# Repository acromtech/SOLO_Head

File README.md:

# SOLO_Head

## Assembly

<br>*Note : Equations can be used to re-size head diameter*

## Design Parts
| CAO | Print | Printing time | Name | Filament | Comment |
|:---:|:---:|---|---|---|---|
|  |  | 9h | 1x Head_Top | ABS | 45° touching buildplate supports required (use soluble supports is better) |
|  | | 1min | 1x Head_Joint | Neoprene | made with laser cutter machine |
|  || 33min | 2x Microphone_Joint | TPU | 45° touching buildplate supports required (use soluble supports is better) |
|  || 20min | 4x Camera_Spacer<br>4x CM4_Spacer<br>8x uDriver_Spacer | ABS | No support required |
|  |  | 1h | 1x Board_Mount | ABS | No support required |
|  |  | 5min | 1x End_Stop | ABS | No support required |
|  | | 1h30 | 1x Encoder_Mount | ABS | No support required |
|  |  | 20min | 1x Encoder_Adaptator | ABS | No support required |
|  |  | 12h | 1x Head_Bottom | ABS | 45° touching buildplate supports required (use soluble supports is better) |
|  || 4h | 1x Head_Stand | ABS | No support required but print with soluble support is better |

## Generic Parts
| Screen | Reference | Link | Comment |
|:---:|---|---|---|
||1x 6700-2RS ball bearing<br>Ø10xØ15x4mm|[123Roulement](https://www.123roulement.com/roulements-6700-2RS)|To link "Encoder_Mount" and "Encoder_Adaptator" design parts|
||8x TCHC M3x8 Screw|[Fixnvis](https://www.visseriefixations.fr/vis-a-six-pans-creux/tete-fraisee-hexagonale-creuse/inox-a4/tfhc-m3x8-inox-a4-ef-din-7991.html)|To link "Encoder_Mount" design part and the motor<br>To link "Encoder_Mount" and "Head_Bottom" design parts|
||4x TCHC M2.5x20 Screw|[Fixnvis](https://www.visseriefixations.fr/vis-a-six-pans-creux/tete-fraisee-hexagonale-creuse/inox-a4/tfhc-m2-5x20-inox-a4-din-7991.html)|To link "Board_Mount" with spacers and "Head_Bottom" design parts|
||1x AEDB-9140-A13 Broadcom Encoder|[RS](https://fr.rs-online.com/web/p/codeurs/7967806?cm_mmc=FR-PLA-DS3A-_-google-_-CSS_FR_FR_Automatisme_et_Controle_de_process_Whoop-_-(FR:Whoop!)+Codeurs-_-7967806&matchtype=&pla-371581285844&gclid=Cj0KCQjw4uaUBhC8ARIsANUuDjVO7Ht5YMR8SH6bczQU4esH6yAVaWhDGcGdfncjnVxadasoeFgfhUsaAsJuEALw_wcB&gclsrc=aw.ds)|/|
||1x GB4106 Tmotor motor|[Hexadrone](https://hexadrone.fr/gamme-gimbal-nacelle/509-moteur-brushless-nacelle-gb4106-tmotor-6971360351184.html)|/|
||1x Arducam 2MP Global Shutter OG02B10 Pivariety camera module |[Robotshop](https://www.robotshop.com/be/fr/module-camera-couleur-arducam-2mp-global-shutter-og02b10-pivariety.html)|/|
||1x ArduCam M12 camera lens (6pcs)|[Robotshop](https://www.robotshop.com/be/fr/kit-objectif-arducam-m12-pour-camera-hq-20-180deg-6pcs.html)|/|
||1x CM4 Raspberry Pi|[Kubii](https://www.kubii.fr/cartes-raspberry-pi/3086-raspberry-pi-compute-module-4-3272496302952.html)|/|
||2x Microphone module|/|Electronic CAD are in the repository "hardware"|
||2x uDriver board||[ODRI repository](https://github.com/open-dynamic-robot-initiative/open_robot_actuator_hardware/blob/master/electronics/micro_driver_electronics/README.md#micro-driver-electronics)|
||2x DF13-5S-1.25C Hirose connector|[RS components](https://fr.rs-online.com/web/p/boitiers-de-connecteurs-pour-circuits-imprimes/1113616)|To link uDriver and communication cables<br>To link CM4 Raspberry Pi and communication cables|
||1x DF13-5P-1.25DS Hirose connector|[RS components](https://fr.rs-online.com/web/p/embases-circuits-imprimes/7793529)|To change encoder connector|
||1x DF13-5P-1.25DSA Hirose connector|[RS components](https://fr.rs-online.com/web/p/embases-circuits-imprimes/5037912)|To link head CM4 Raspberry Pi shield communication cables to body Raspberry Pi communication cables|
||1x RE-6619107 XT30U 2 mm Reely Male  connector|[Conrad](https://www.conrad.fr/p/reely-re-6619107-fiche-male-pour-batterie-xt30u-2-mm-femelle-doree-a-souder-1-pcs-2206369)|To link power cables to uDriver board|
||1x RE-6619104 XT30U 2 mm Reely Female connector|[Conrad](https://www.conrad.fr/p/reely-re-6619107-fiche-male-pour-batterie-xt30u-2-mm-femelle-doree-a-souder-1-pcs-2206369)|To link power cables to power board (on SOLO body)|
||1x Kabeltronik 160110009-1 1mm² Black Power Wire|[Conrad](https://www.conrad.com/p/kabeltronik-160110009-1-strand-lify-1-x-1-mm-black-sold-per-metre-323735)|To power uDriver board|
||1x Kabeltronik 160110008 1mm² Red Power Wire|[Conrad](https://www.conrad.fr/p/fil-de-cablage-lify-kabeltronik-160110008-1-1-x-1-mm-rouge-marchandise-vendue-au-metre-323734)|To power uDriver board|
||1x 10 way 3M 3302-10 100FT communication cables |[RS components](https://fr.rs-online.com/web/p/cables-en-nappe/1055281)|To link encoder and uDriver (5 way)<br>To link CM4 Raspberry Pi and uDriver (5 way)|
||1x DF13-2630SCF 0.12mm² Hirose DF13 Crimp Terminals|[RS components](https://fr.rs-online.com/web/p/cables-en-nappe/1055281)|To link communication cables with DF13-5S-1.25C Hirose connector|
||1x DF13-TB2630HC Hirose Crimping Tool for DF13 Crimp Terminals |[RS components](https://fr.rs-online.com/web/p/cables-en-nappe/1055281)|To link communication cables with DF13-5S-1.25C Hirose connector|

## Next Version (V7)
To reduce mass, clean print, and keep design apparence. I realize some modifications on the V6 design :
* Delete "Head_Joint" neoprene gasket and chamfer "Head_Bottom" and "Head_Top" parts to simplify the model and clean model surface.
* Design a new "Head_Stand" to link the SOLO's head to SOLO's body.
* Delete "Microphone_Joint" and integrate a screwing system on "Head_Bottom" to simplify the model. To limit microphone noise, generic O-rings are positioned on the screw.
* Upgrade clips shape to limit printing supports.

## License
BSD 3-Clause License

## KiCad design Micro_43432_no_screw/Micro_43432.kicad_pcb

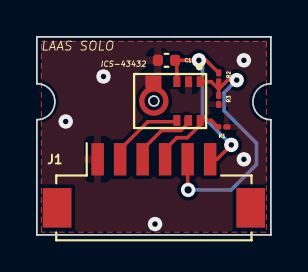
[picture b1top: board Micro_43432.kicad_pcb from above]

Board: 2 copper layers, 13.0 x 11.0 mm, 6 parts (0 on the bottom side), 6 nets.

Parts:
C1: 0.1u; C_0402_1005Metric
J1: Conn_01x06_Female; Hirose_DF13C_CL535-0406-3-51_1x06-1MP_P1.25mm_Vertical
K1: ICS-43432; MIC_ICS-43432
R1: 100k; R_01005_0402Metric
R2: NC; R_01005_0402Metric
R3: 0; R_01005_0402Metric

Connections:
/LR: J1.5, K1.1 (LR), R2.2, R3.1
/SCK: J1.3, K1.6 (SCK)
/SD: J1.4, K1.7 (SD), R1.1
/WS: J1.2, K1.5 (WS)
GND: C1.2, J1.1, K1.2 (CONFIG), K1.4 (GND), R1.2, R3.2
VDD: C1.1, J1.6, K1.3 (VDD), R2.1
